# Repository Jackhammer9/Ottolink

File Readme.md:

### Design and Control of a 4-DoF Anthropomorphic Robotic Manipulator

Ottolink is a custom 4-DoF anthropomorphic robotic manipulator designed and built for spatial end-effector trajectory execution. The project combines mechanical design, embedded real-time control, Jacobian-based inverse kinematics, custom electronics, and MuJoCo simulation into a complete robotic system.

---

## Overview

Ottolink features a **3-DoF shoulder configuration and 1-DoF pitch elbow**, providing spatial control of the end effector.

The project was developed as a complete robotics pipeline:

**CAD → Mechanical Assembly → Kinematics → Simulation → Embedded Control → Custom PCB → Physical Robot**

The controller runs on an **ATmega328P-based embedded system** and executes Cartesian-space trajectories using a Jacobian pseudoinverse controller.

---

### Watch It In Action

You can watch the arm in action on my [Portfolio Website](https://arnav-bajaj.com/projects/15/).

---

## Features

- 4-DoF anthropomorphic robotic arm
- 3-DoF shoulder + 1-DoF pitch elbow
- Custom mechanical design in Autodesk Inventor
- 3D-printable mechanical components
- Jacobian pseudoinverse inverse kinematics
- Real-time Cartesian-space control
- Custom C++ linear algebra library
- Rodrigues rotation formulation for joint-axis transformations
- Multi-axis synchronized PWM servo control
- Joint interpolation and trajectory execution
- Custom control PCB designed in KiCad
- Dedicated power distribution and voltage regulation
- MuJoCo simulation environment
- Simulation-to-hardware trajectory validation

---

# Mechanical Design

The robotic arm was designed and assembled in **Autodesk Inventor**, with component geometry optimized for 3D printing tolerances.

The mechanical design considers:

- Joint clearances
- Structural rigidity
- Servo mounting
- Payload-to-weight considerations
- Assembly constraints
- Joint-axis alignment

The final design was manufactured using 3D-printed components and integrated with the actuator and control system.

### CAD

The [`CAD/`](CAD/) directory contains the mechanical design files and supporting models.

---

# Kinematics and Control

## Jacobian-Based Cartesian Control

Ottolink uses a **Jacobian pseudoinverse controller** to map Cartesian end-effector errors into joint-space corrections.

Given the end-effector error:

```text
e = x_target - x_current
```

the joint-space update is calculated using:

```text
Δq = J⁺ e
```

where:

- `J` is the manipulator Jacobian
- `J⁺` is the Moore-Penrose pseudoinverse
- `e` is the Cartesian position error
- `Δq` is the resulting joint-space correction

The controller iteratively updates the joint configuration to reduce the Cartesian position error and converge toward the target trajectory.

---

## Rodrigues Rotation

Rodrigues' rotation formula is used to represent arbitrary rotations around the robot's joint axes.

This is particularly important for handling the physical robot's non-ideal axis configurations and maintaining consistency between:

- The CAD model
- The mathematical kinematic model
- The MuJoCo simulation
- The physical robot

---

## Custom Linear Algebra Library

A lightweight custom C++ matrix and linear algebra library was developed specifically for the ATmega328P.

The library provides the operations required by the real-time controller, including:

- Matrix multiplication
- Matrix transposition
- Matrix inversion
- Pseudoinverse operations
- Vector operations

The implementation was designed around the memory and computational constraints of the ATmega328P rather than relying on a large external numerical library.

---

# Embedded Controller

The physical robot is controlled by an **ATmega328P-based embedded system**.

The firmware provides:

- Multi-axis PWM control
- Synchronized servo actuation
- Joint interpolation
- Cartesian trajectory execution
- Real-time kinematic calculations
- Joint-space corrections

The controller was implemented using C++ and PlatformIO.

### Firmware

The embedded controller can be found in:

```text
OttolinkController/
```

The main source code is located in:

```text
OttolinkController/src/
```

---

# Electronics

A custom control PCB was designed in **KiCad**.

The PCB provides:

- Servo power distribution
- Localized voltage regulation
- High-current actuator power handling
- Separation of actuator power from logic-level control signals
- Centralized connections between the microcontroller and actuators

The board was designed to reduce wiring complexity while providing a more robust electrical interface for the robotic system.

### PCB Design

PCB source files are available in:

```text
OttolinkPCB/
```

The directory contains the KiCad schematic, PCB layout, project files, and custom footprint data required for the board.

Manufacturing files are available in:

```text
PCBGerberFiles/
```

---

# Simulation

A complete **MuJoCo simulation** of the robotic arm was developed to validate the kinematic and control system before deployment to the physical hardware.

The simulation includes:

- Robot geometry
- Coordinate frames
- Joint definitions
- Joint limits
- Kinematic transformations
- End-effector control
- Cartesian trajectory execution

The simulation files are located in:

```text
Sim/
├── meshes/
├── ottolink.xml
└── OttolinkSimulation.py
```

The simulation was used to validate:

1. Forward kinematics
2. Coordinate-frame transformations
3. Jacobian calculations
4. Jacobian pseudoinverse control
5. Cartesian trajectory generation
6. Controller behavior prior to physical deployment

---

# Simulation-to-Hardware Workflow

The project was developed with a simulation-first workflow.

```text
        Mechanical Design
               │
               ▼
        Kinematic Model
               │
               ▼
         MuJoCo Model
               │
               ▼
      Controller Validation
               │
               ▼
      Embedded Implementation
               │
               ▼
       Physical Robot
```

This workflow allowed the kinematic and trajectory-control algorithms to be tested in simulation before being executed on the embedded controller and physical hardware.

---

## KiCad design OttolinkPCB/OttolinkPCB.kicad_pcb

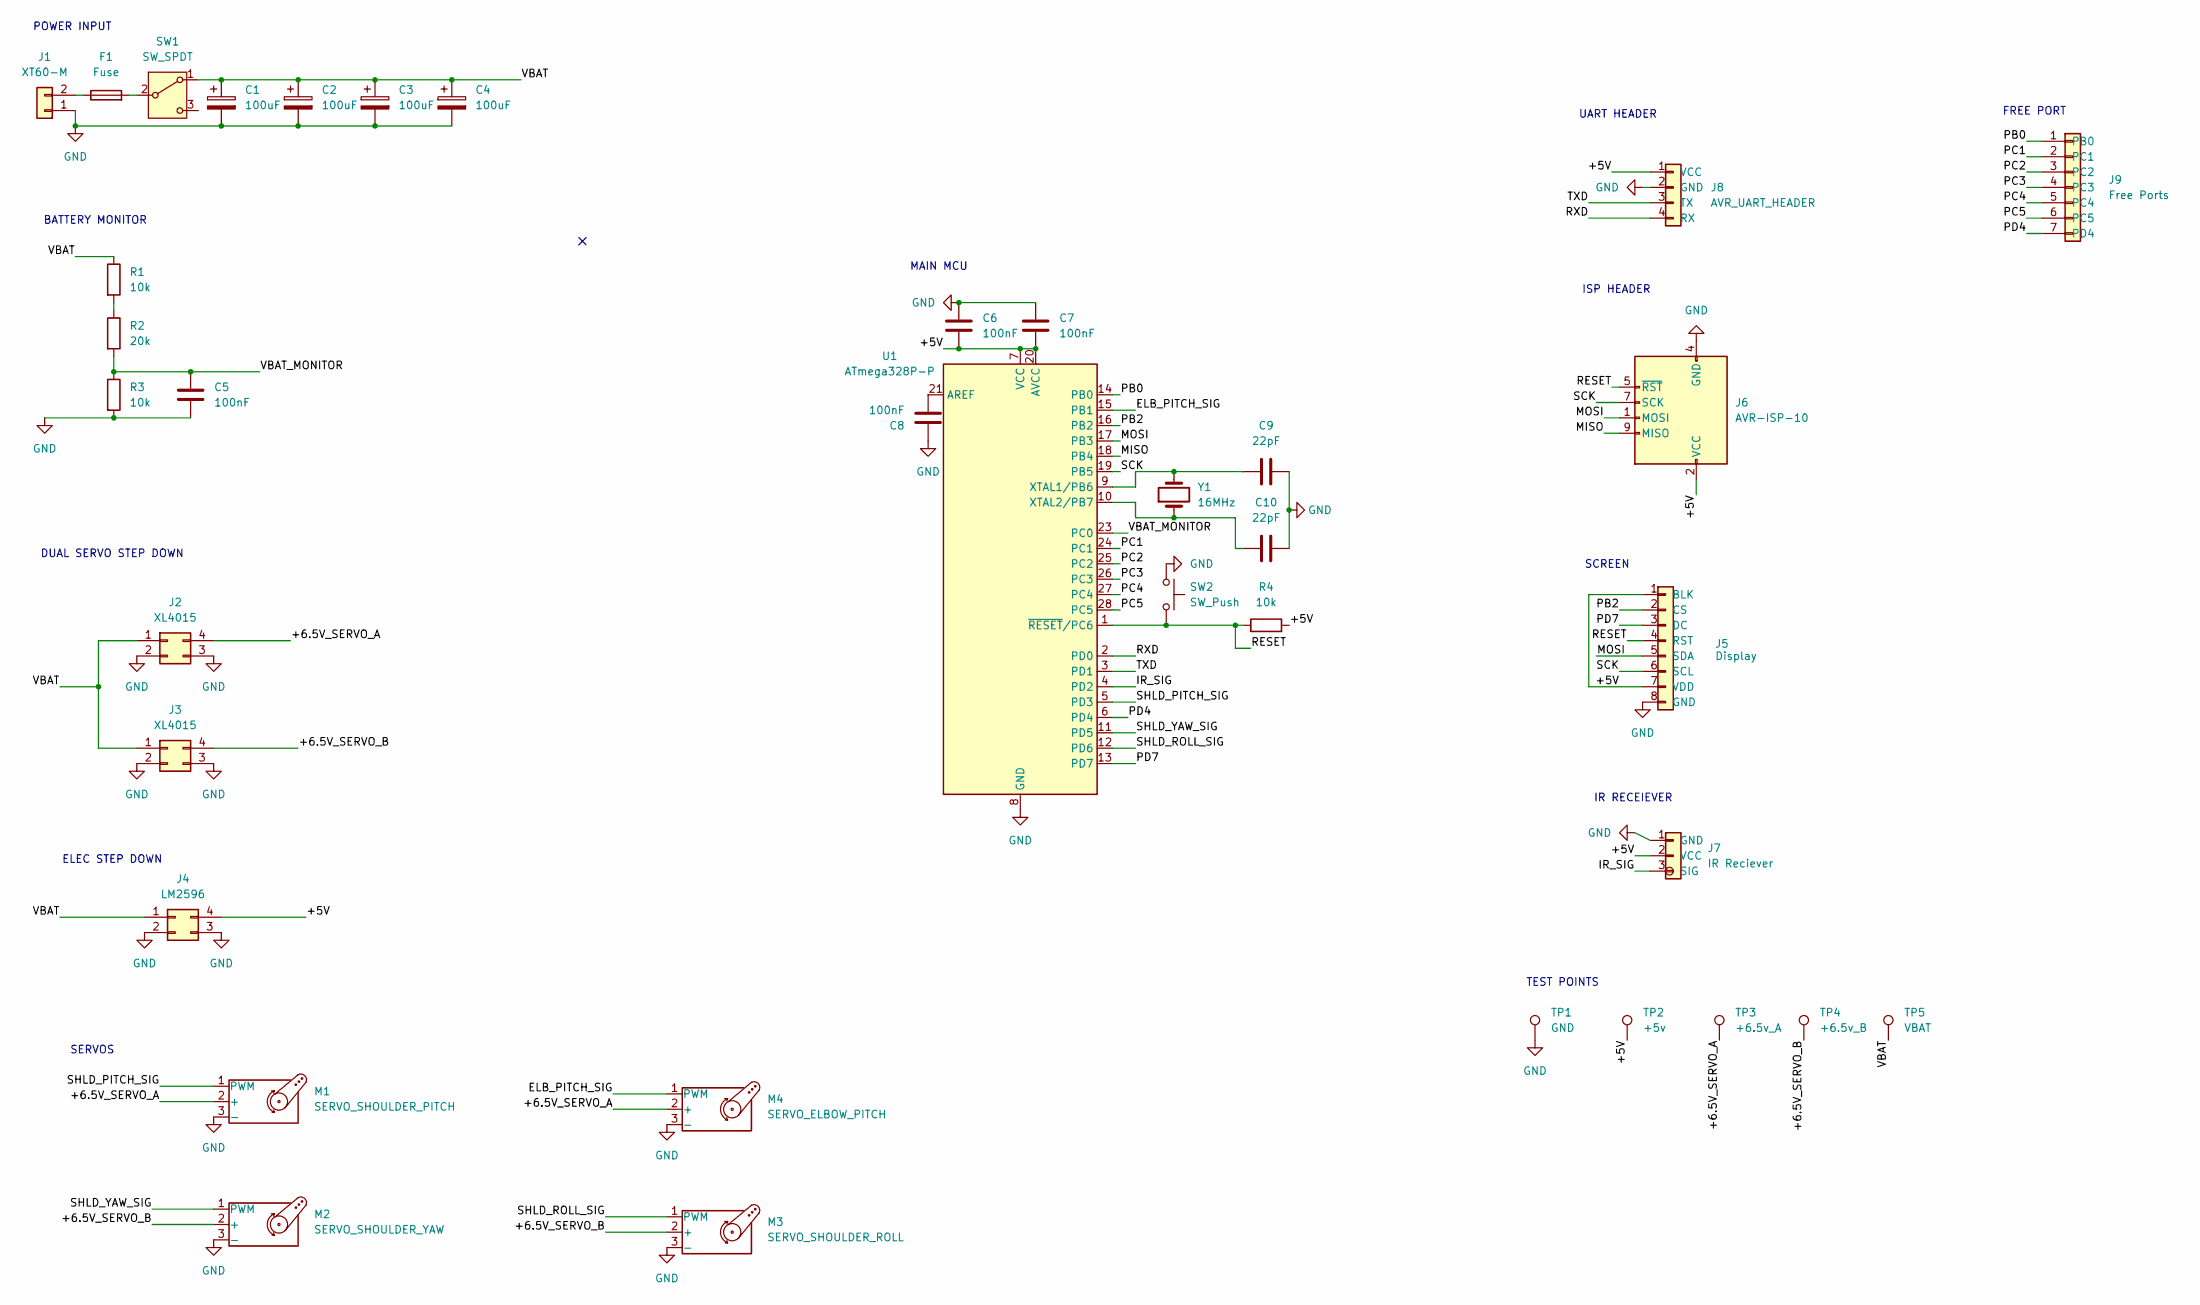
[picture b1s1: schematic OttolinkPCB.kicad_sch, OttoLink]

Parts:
C1, C2, C3, C4: 100uF; CP_Radial_D5.0mm_P2.00mm
C5, C6, C7, C8: 100nF; C_0805_2012Metric_Pad1.18x1.45mm_HandSolder
C9, C10: 22pF; C_Disc_D5.0mm_W2.5mm_P5.00mm
F1: Fuse; Fuseholder_Cylinder-5x20mm_Schurter_0031_8201_Horizontal_Op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
J1: XT60-M; AMASS_XT60-M_1x02_P7.20mm_Vertical
J2, J3: XL4015
J4: LM2596; LM2596 Step Down Module
J5: Display; PinHeader_1x08_P2.54mm_Vertical
J6: AVR-ISP-10; PinHeader_2x05_P2.54mm_Vertical
J7: IR Reciever; PinHeader_1x03_P2.54mm_Vertical
J8: AVR_UART_HEADER; PinHeader_1x04_P2.54mm_Vertical
J9: Free Ports; PinHeader_1x07_P2.54mm_Vertical
M1: SERVO_SHOULDER_PITCH; PinHeader_1x03_P2.54mm_Vertical
M2: SERVO_SHOULDER_YAW; PinHeader_1x03_P2.54mm_Vertical
M3: SERVO_SHOULDER_ROLL; PinHeader_1x03_P2.54mm_Vertical
M4: SERVO_ELBOW_PITCH; PinHeader_1x03_P2.54mm_Vertical
R1, R3, R4: 10k; R_Axial_DIN0207_L6.3mm_D2.5mm_P7.62mm_Horizontal
R2: 20k; R_Axial_DIN0207_L6.3mm_D2.5mm_P7.62mm_Horizontal
SW1: SW_SPDT; PinHeader_1x03_P2.54mm_Vertical
SW2: SW_Push; SW_PUSH_6mm
TP1: GND; TestPoint_Pad_D2.0mm
TP2: +5v; TestPoint_Pad_D2.0mm
TP3: +6.5v_A; TestPoint_Pad_D2.0mm
TP4: +6.5v_B; TestPoint_Pad_D2.0mm
TP5: VBAT; TestPoint_Pad_D2.0mm
U1: ATmega328P-P; DIP-28_W7.62mm
Y1: 16MHz; Crystal_HC49-4H_Vertical

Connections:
/+5V: C6.2, C7.2, J4.4, J5.1 (BLK), J5.7 (VDD), J6.2 (VCC), J7.2 (VCC), J8.1 (VCC), R4.2, TP2.1 (1_1), U1.7 (VCC), U1.20 (AVCC)
/+6.5V_SERVO_A: J2.4, M1.2 (+), M4.2 (+), TP3.1 (1_1)
/+6.5V_SERVO_B: J3.4, M2.2 (+), M3.2 (+), TP4.1 (1_1)
/ELB_PITCH_SIG: M4.1 (PWM), U1.15 (PB1)
/IR_SIG: J7.3 (SIG), U1.4 (PD2)
/MISO: J6.9 (MISO), U1.18 (PB4)
/MOSI: J5.5 (SDA), J6.1 (MOSI), U1.17 (PB3)
/PB0: J9.1 (PB0), U1.14 (PB0)
/PB2: J5.2 (CS), U1.16 (PB2)
/PC1: J9.2 (PC1), U1.24 (PC1)
/PC2: J9.3 (PC2), U1.25 (PC2)
/PC3: J9.4 (PC3), U1.26 (PC3)
/PC4: J9.5 (PC4), U1.27 (PC4)
/PC5: J9.6 (PC5), U1.28 (PC5)
/PD4: J9.7 (PD4), U1.6 (PD4)
/PD7: J5.3 (DC), U1.13 (PD7)
/RESET: J5.4 (RST), J6.5 (~RST), R4.1, SW2.2, U1.1 (~RESET/PC6)
/RXD: J8.4 (RX), U1.2 (PD0)
/SCK: J5.6 (SCL), J6.7 (SCK), U1.19 (PB5)
/SHLD_PITCH_SIG: M1.1 (PWM), U1.5 (PD3)
/SHLD_ROLL_SIG: M3.1 (PWM), U1.12 (PD6)
/SHLD_YAW_SIG: M2.1 (PWM), U1.11 (PD5)
/TXD: J8.3 (TX), U1.3 (PD1)
/VBAT: C1.1, C2.1, C3.1, C4.1, J2.1, J3.1, J4.1, R1.1, SW1.1 (A), TP5.1 (1_1)
/VBAT_MONITOR: C5.1, R2.2, R3.1, U1.23 (PC0)
GND: C1.2, C2.2, C3.2, C4.2, C5.2, C6.1, C7.1, C8.1, C9.2, C10.1, J1.1, J2.2, J2.3, J3.2, J3.3, J4.2, J4.3, J5.8 (GND), J6.4 (GND), J6.6 (GND), J6.8 (GND), J6.10 (GND), J7.1 (GND), J8.2 (GND), M1.3 (-), M2.3 (-), M3.3 (-), M4.3 (-), R3.2, SW2.1, TP1.1 (1_1), U1.8 (GND), U1.22 (GND)
unnamed: F1.1, J1.2
unnamed: R1.2, R2.1
unnamed: F1.2, SW1.2 (B)
unnamed: C8.2, U1.21 (AREF)
unnamed: C9.1, U1.9 (XTAL1/PB6), Y1.2
unnamed: C10.2, U1.10 (XTAL2/PB7), Y1.1

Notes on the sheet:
DUAL SERVO STEP DOWN
BATTERY MONITOR
TEST POINTS
IR RECEIEVER
FREE PORT
SCREEN
ELEC STEP DOWN
MAIN MCU
SERVOS
POWER INPUT
ISP HEADER
UART HEADER

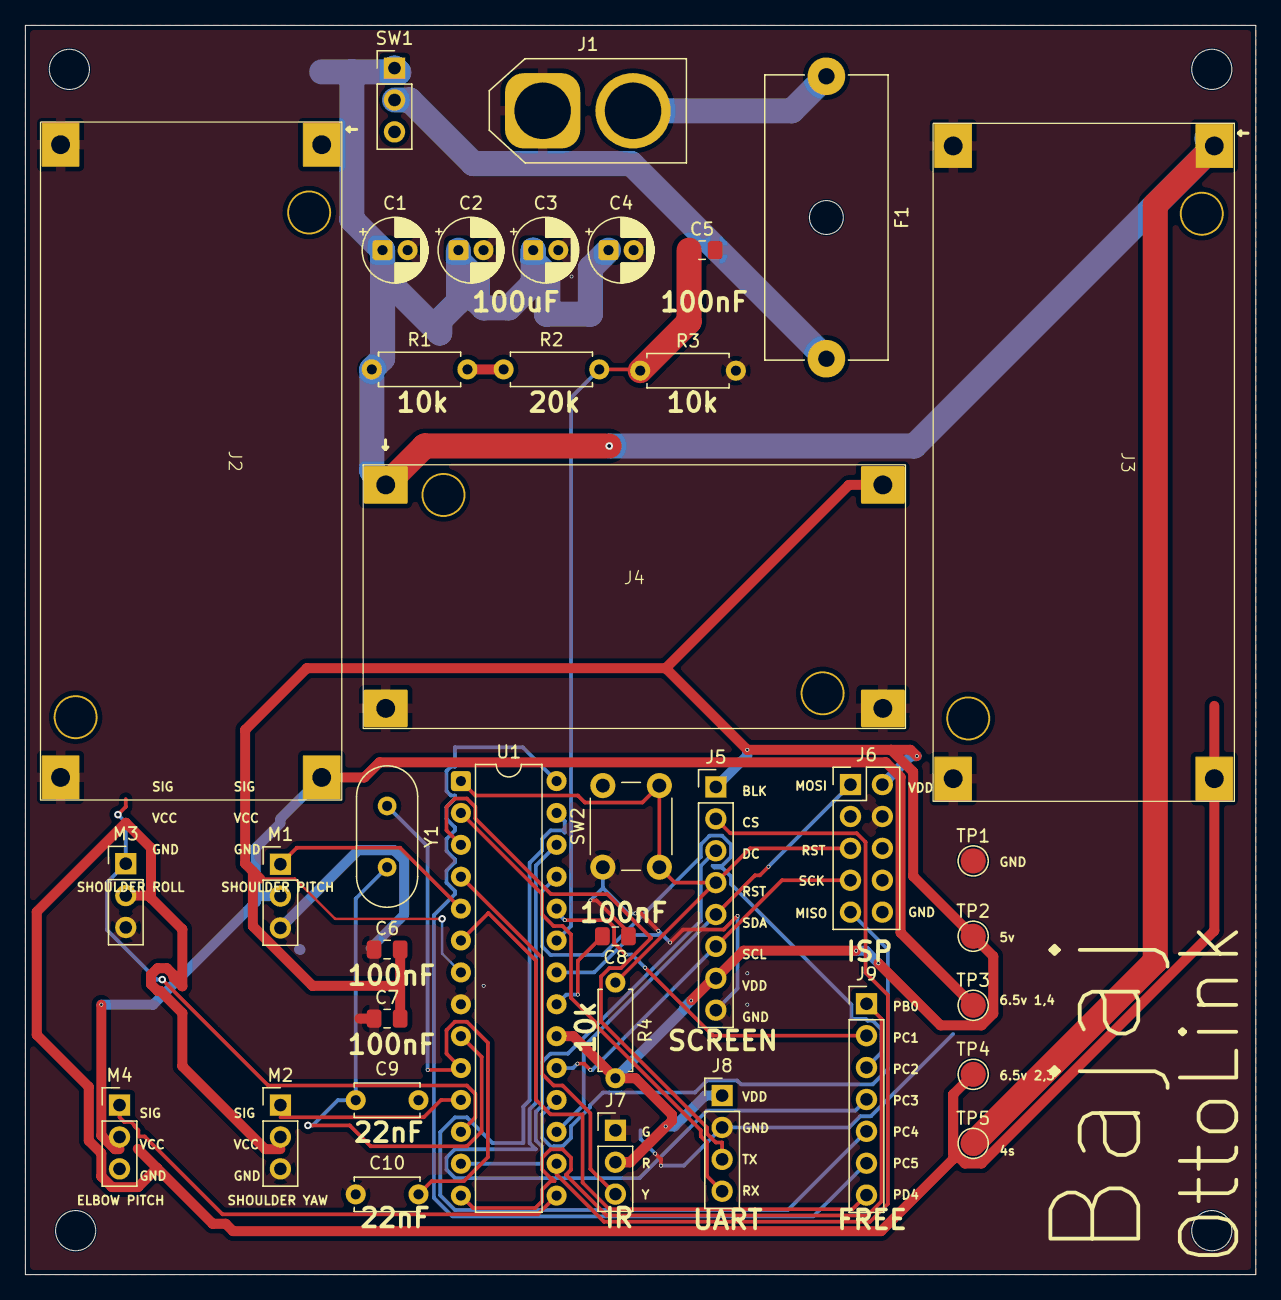
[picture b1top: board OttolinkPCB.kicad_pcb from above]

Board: 2 copper layers, 98.0 x 99.5 mm, 37 parts (0 on the bottom side), 32 nets.
